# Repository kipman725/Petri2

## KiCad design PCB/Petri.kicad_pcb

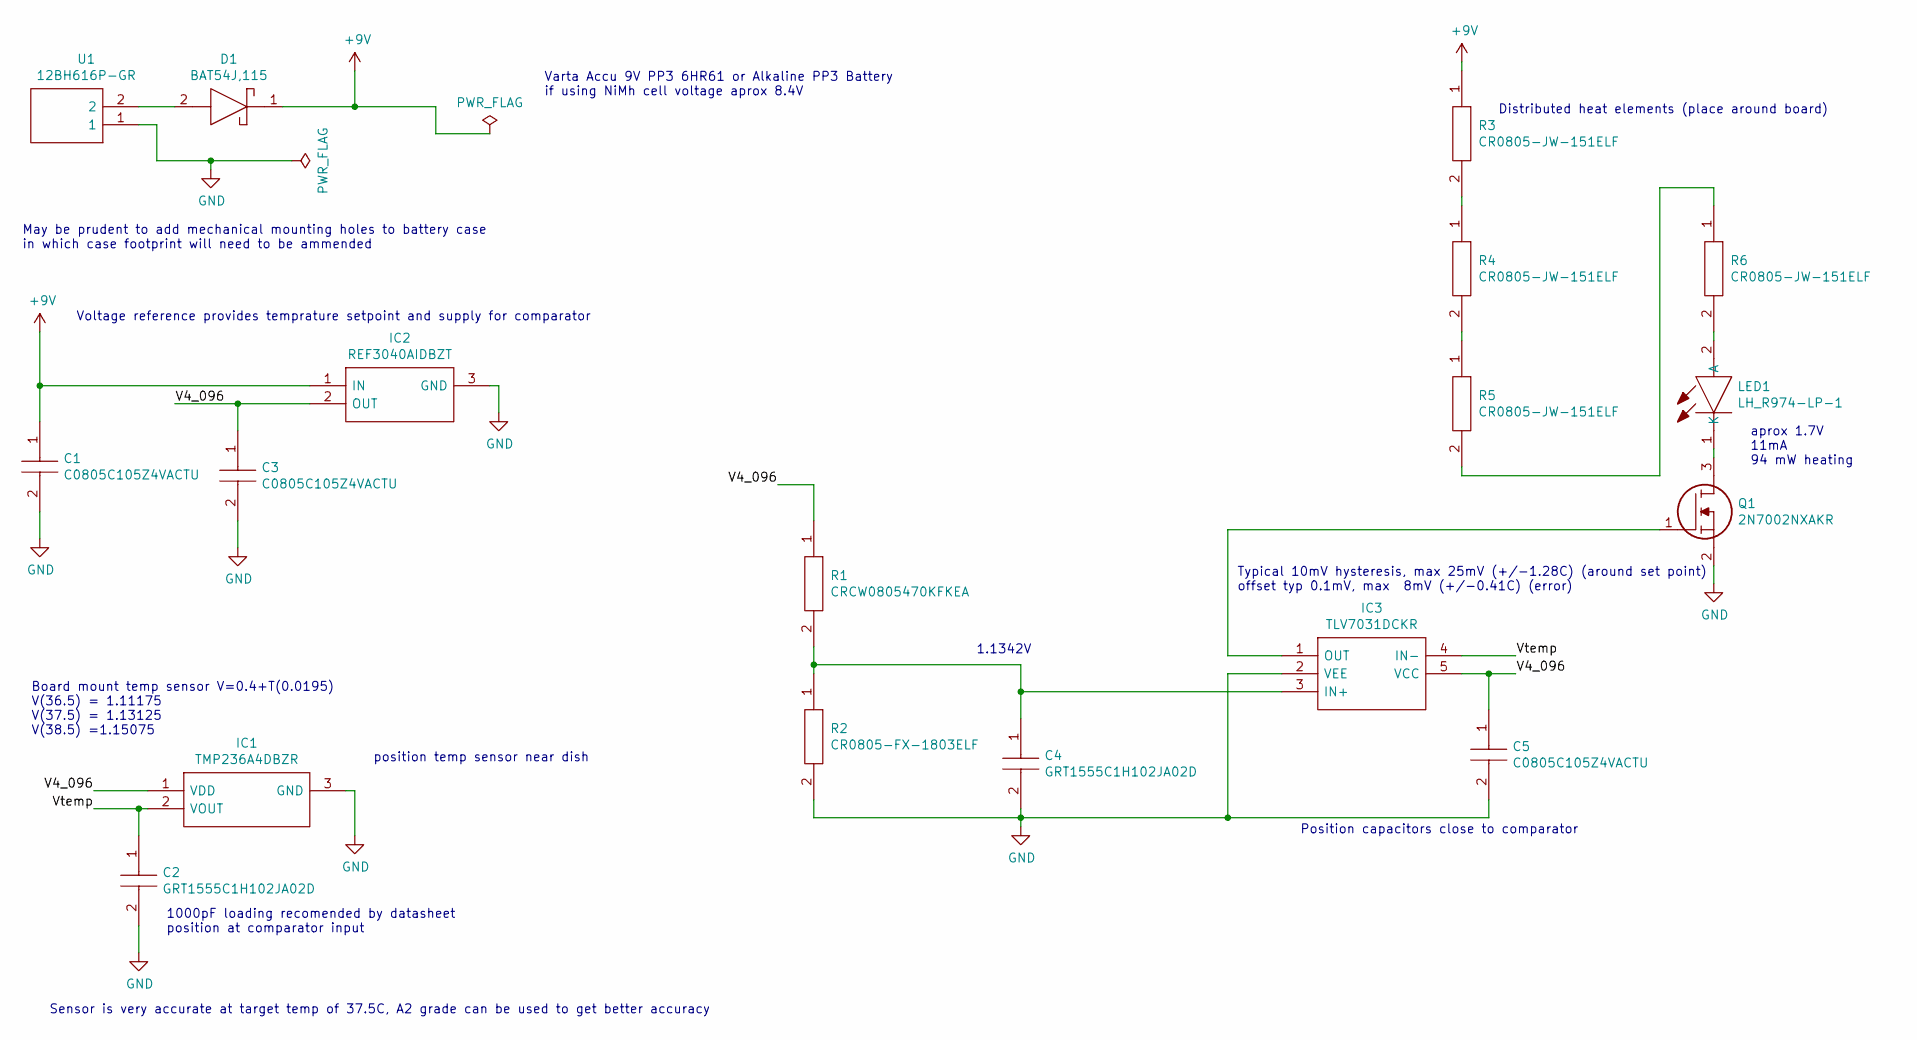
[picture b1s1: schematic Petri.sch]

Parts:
C1, C3, C5: C0805C105Z4VACTU; CAPC2013X140N; Mouser Part Number 80-C0805C105Z4V
C2, C4: GRT1555C1H102JA02D; CAPC1005X55N; Mouser Part Number 81-GRT1555C1H102JA2D
D1: BAT54J,115; SODFL2512X80N; Mouser Part Number 771-BAT54J115
IC1: TMP236A4DBZR; SOT95P237X112-3N; Mouser Part Number 595-TMP236A4DBZR
IC2: REF3040AIDBZT; SOT95P237X112-3N; Mouser Part Number 595-REF3040AIDBZT
IC3: TLV7031DCKR; SOT65P210X110-5N; Mouser Part Number 595-TLV7031DCKR
LED1: LH_R974-LP-1; LEDC2012X90N; Mouser Part Number 720-LHR974-LP-1
Q1: 2N7002NXAKR; SOT95P230X110-3N; Mouser Part Number 771-2N7002NXAKR
R1: CRCW0805470KFKEA; RESC2012X50N; Mouser Part Number 71-CRCW0805470KFKEA
R2: CR0805-FX-1803ELF; RESC2012X60N; Mouser Part Number 652-CR0805FX-1803ELF
R3, R4, R5, R6: CR0805-JW-151ELF; RESC2012X60N; Mouser Part Number 652-CR0805JW-151ELF
U1: 12BH616P-GR; 12BH616PGR; Mouser Part Number 12BH616P-GR

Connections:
+9V: C1.1, D1.1, IC2.1 (IN), R3.1
/V4_096: C3.1, C5.1, IC1.1 (VDD), IC2.2 (OUT), IC3.5 (VCC), R1.1
/Vtemp: C2.1, IC1.2 (VOUT), IC3.4 (IN-)
GND: C1.2, C2.2, C3.2, C4.2, C5.2, IC1.3 (GND), IC2.3 (GND), IC3.2 (VEE), Q1.2, R2.2, U1.1
unnamed: C4.1, IC3.3 (IN+), R1.2, R2.1
unnamed: D1.2, U1.2
unnamed: IC3.1 (OUT), Q1.1
unnamed: LED1.1 (K), Q1.3
unnamed: LED1.2 (A), R6.2
unnamed: R3.2, R4.1
unnamed: R4.2, R5.1
unnamed: R5.2, R6.1

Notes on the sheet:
Varta Accu 9V PP3 6HR61 or Alkaline PP3 Battery if using NiMh cell voltage aprox 8.4V
May be prudent to add mechanical mounting holes to battery case in which case footprint will need to be ammended
Voltage reference provides temprature setpoint and supply for comparator
Board mount temp sensor V=0.4+T(0.0195) V(36.5) = 1.11175 V(37.5) = 1.13125 V(38.5) =1.15075
1000pF loading recomended by datasheet position at comparator input
Typical 10mV hysteresis, max 25mV (+/-1.28C) (around set point) offset typ 0.1mV, max 8mV (+/-0.41C) (error)
Sensor is very accurate at target temp of 37.5C, A2 grade can be used to get better accuracy
1.1342V
Position capacitors close to comparator
Distributed heat elements (place around board)
aprox 1.7V 11mA 94 mW heating
position temp sensor near dish

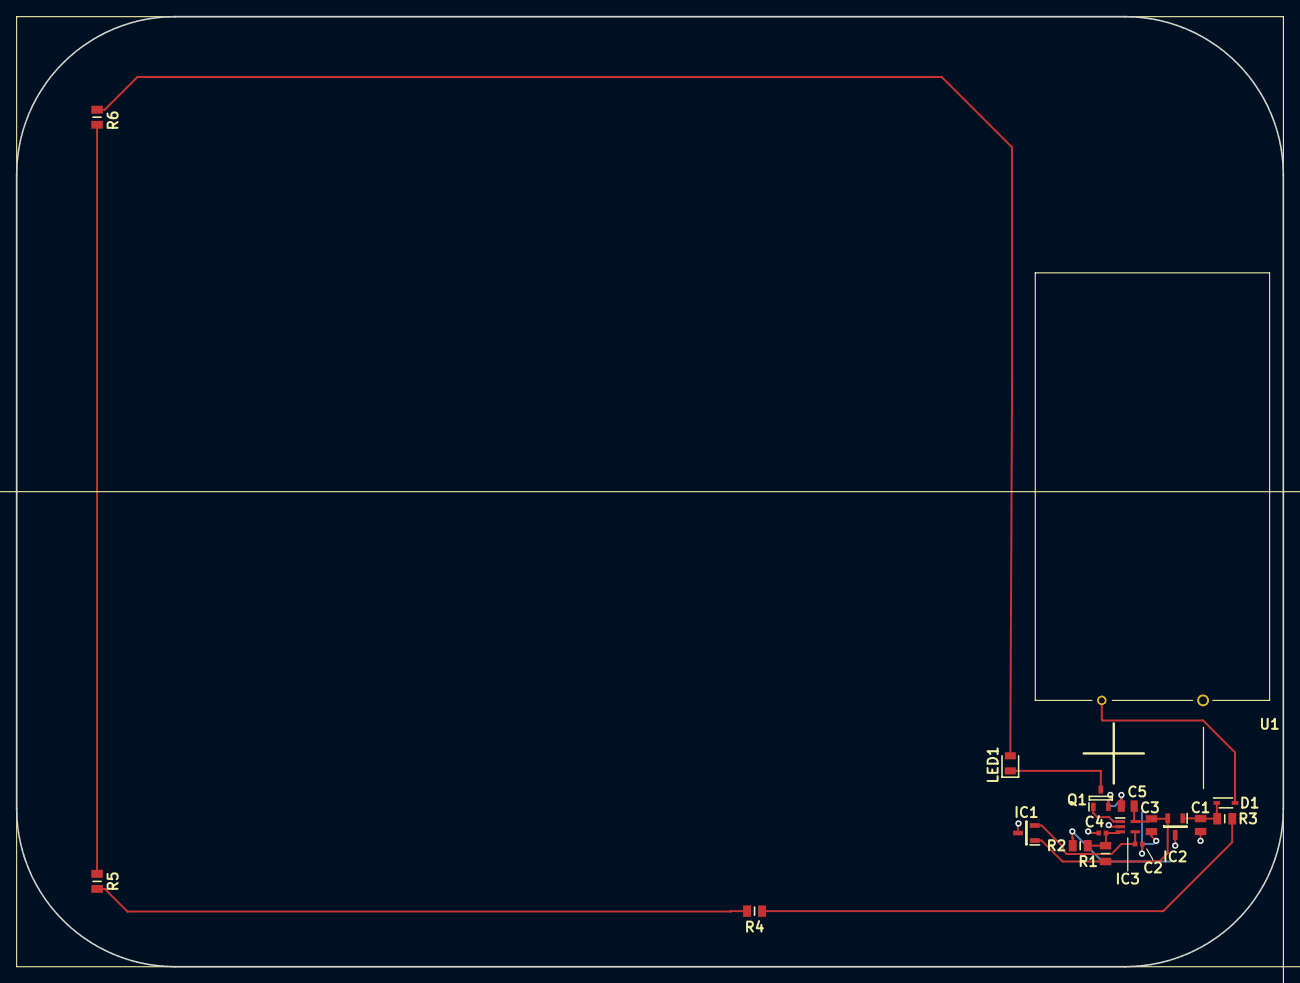
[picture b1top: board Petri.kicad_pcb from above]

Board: 2 copper layers, 160.0 x 120.0 mm, 18 parts (0 on the bottom side), 12 nets.

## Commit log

2020-06-28 Added dxf for real
    :)
2020-06-28 Update projection_holes.dxf
    uploaded the right file this time
2020-06-29 added models
    need to design cover after components are in place
2020-06-29 PCB
    should add pcb
2020-06-29 PCB
    Fixed nested git error should now work
2020-06-30 Updated PCB
    work completed:
    - added proper dxf edge cuts from fusion file
    - rerouted some tracks and positioned battery
    to be done:
    - position battery holder exactly at ½ height
    - add cuts for case (staggered?)
